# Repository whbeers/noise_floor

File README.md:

# Noise Floor interface board collection

This is set of interface boards to speed effect pedal development, continuing my efforts to learn PCB design with [KiCAD](https://www.kicad.org/).

### IO and Switch boards
The first board is an audio input and power board, featuring:
  - Switched DC barrel jack supporting either a 9VDC center negative supply or 9V battery
  - Mono audio jacks w/ switched input circuit (ring/ground shorted to sleeve on insertion)
  - Basic power input protection

The IO PCB is designed to fit in a standard 125B enclosure.

The second board simplifies effect bypass via a 3PDT switch adapter with an LED indicator.

#### Connectivity (cabled)
IO, Effect, and Switch boards are connected using four-circuit [Molex PicoBlade](https://www.molex.com/molex/products/family/picoblade?parentKey=wire_to_board_connectors) connectors.

Headers are labelled symmetrically from the perspective of the IO board:
 - **S**1 on IO Board <-> **S**1 on **S**witch Board
 - **S**2 on IO Board <-> **S**2 on **S**witch Board
 - **E**1 on IO Board <-> **E**1 on **E**ffect Board

### UX PCB (experimental)
The third and newest (experimental) board is a UX board providing a standard superset of potentiometers and switches. It is intended to connect to an effects board using two 25-position [Amphenol "Conan Lite"](https://www.amphenol-cs.com/product-series/conan-lite-1-00mm.html) board-to-board connectors.

The current iteration of the UX board supports six potentiometers and three SPDT switches, but alternative control layouts are an obvious extension. Each potentiometer on the current prototype can be adjusted using optional parallel resistors (SMD 1206) to tweak the taper and total resistance.

#### Connectivity (board-to-board)
The effect and UX boards are connected using [Amphenol "Conan Lite"](https://www.amphenol-cs.com/product-series/conan-lite-1-00mm.html) board-to-board connectors. Only a single UX board variety currently exists, supporting a superset of six potentiometers and three SPDT switches. As the UX board is in the experimental/proof-of-concept phase, the pin assignment should be considered preliminary and subject to change.

Current connector allocation:
 - 6x Potentiometers x 3 (CCW, Wiper, CW) = 18
 - 3x SPDT switches x 3 (NO, COM, NC) = 9
 - 4x Reserved for ground
 - Total used: 31
 - Remaining for expansion: 19
 
Ideas for future boards / changes:
 - Allocate connector positions for a single DPDT switch (+3, reusing 3 from an existing SPDT)
 - Incorporate linear potentiometers into an alternate IO board
 - Allocate at least 12 positions for "flexible use" (enough to support a 4PDT switch)
 - Allocate positions to drive (RGB?) LEDs with standardized current-limiting resistors

[Schematic PDF](schematics/noise_floor-latest.pdf)

## Credit

The original idea and specific bypass circuit is inspired by many manufacturers of utility PCBs and well-known circuits for 3PDT-based effect bypass, notably [PedalPCB's 3PDT breakout](https://www.pedalpcb.com/product/3pdt/), augmented to suit my needs.

Thanks as always to the folks on the [freestompboxes.org](https://www.freestompboxes.org/) forum for feedback and suggestions.

Potentiometer, 3PDT footswitch, and DC barrel jack 3D models courtesy [Vasily Kashirin](https://grabcad.com/vasily.kashirin-1).

SPDT toggle switch 3D model courtesy [Stephanie Schwecke](https://grabcad.com/stephanie.schwecke-1).

Conan Lite footprints adapted from the 51-position footprints available from SnapEDA: [Header](https://www.snapeda.com/parts/10162582-1134151LF/Amphenol%20ICC%20(FCI)/view-part/), [Receptacle](https://www.snapeda.com/parts/10162581-3134151LF/Amphenol%20ICC%20(FCI)/view-part/).([Additional license details](hardware/SnapEDA_Licensing.txt)). 3D models courtesy Amphenol.

*I am not affiliated with any of the brands, sites, or products named in this overview.*

## Future plans

 - Build an IO board that includes a TRS expression pedal input (started this way, but found it hard to fit in a 125B enclosure)
 - Support stereo operation via relays, optoisolators, or a "millenium" switch

## Versioning

My pcb designs utilize the following versioning scheme (I'll add to this as I produce more revisions):
 - v0.0XX: A candidate design that has not yet been produced and tested.
 - v0.XX: A design that has been produced, tested, and any initial errors addressed.

## Name
*The name Noise Floor is a reflection of the function of the board (a substrate for pedals and bypass circuit) and security nerdery.*

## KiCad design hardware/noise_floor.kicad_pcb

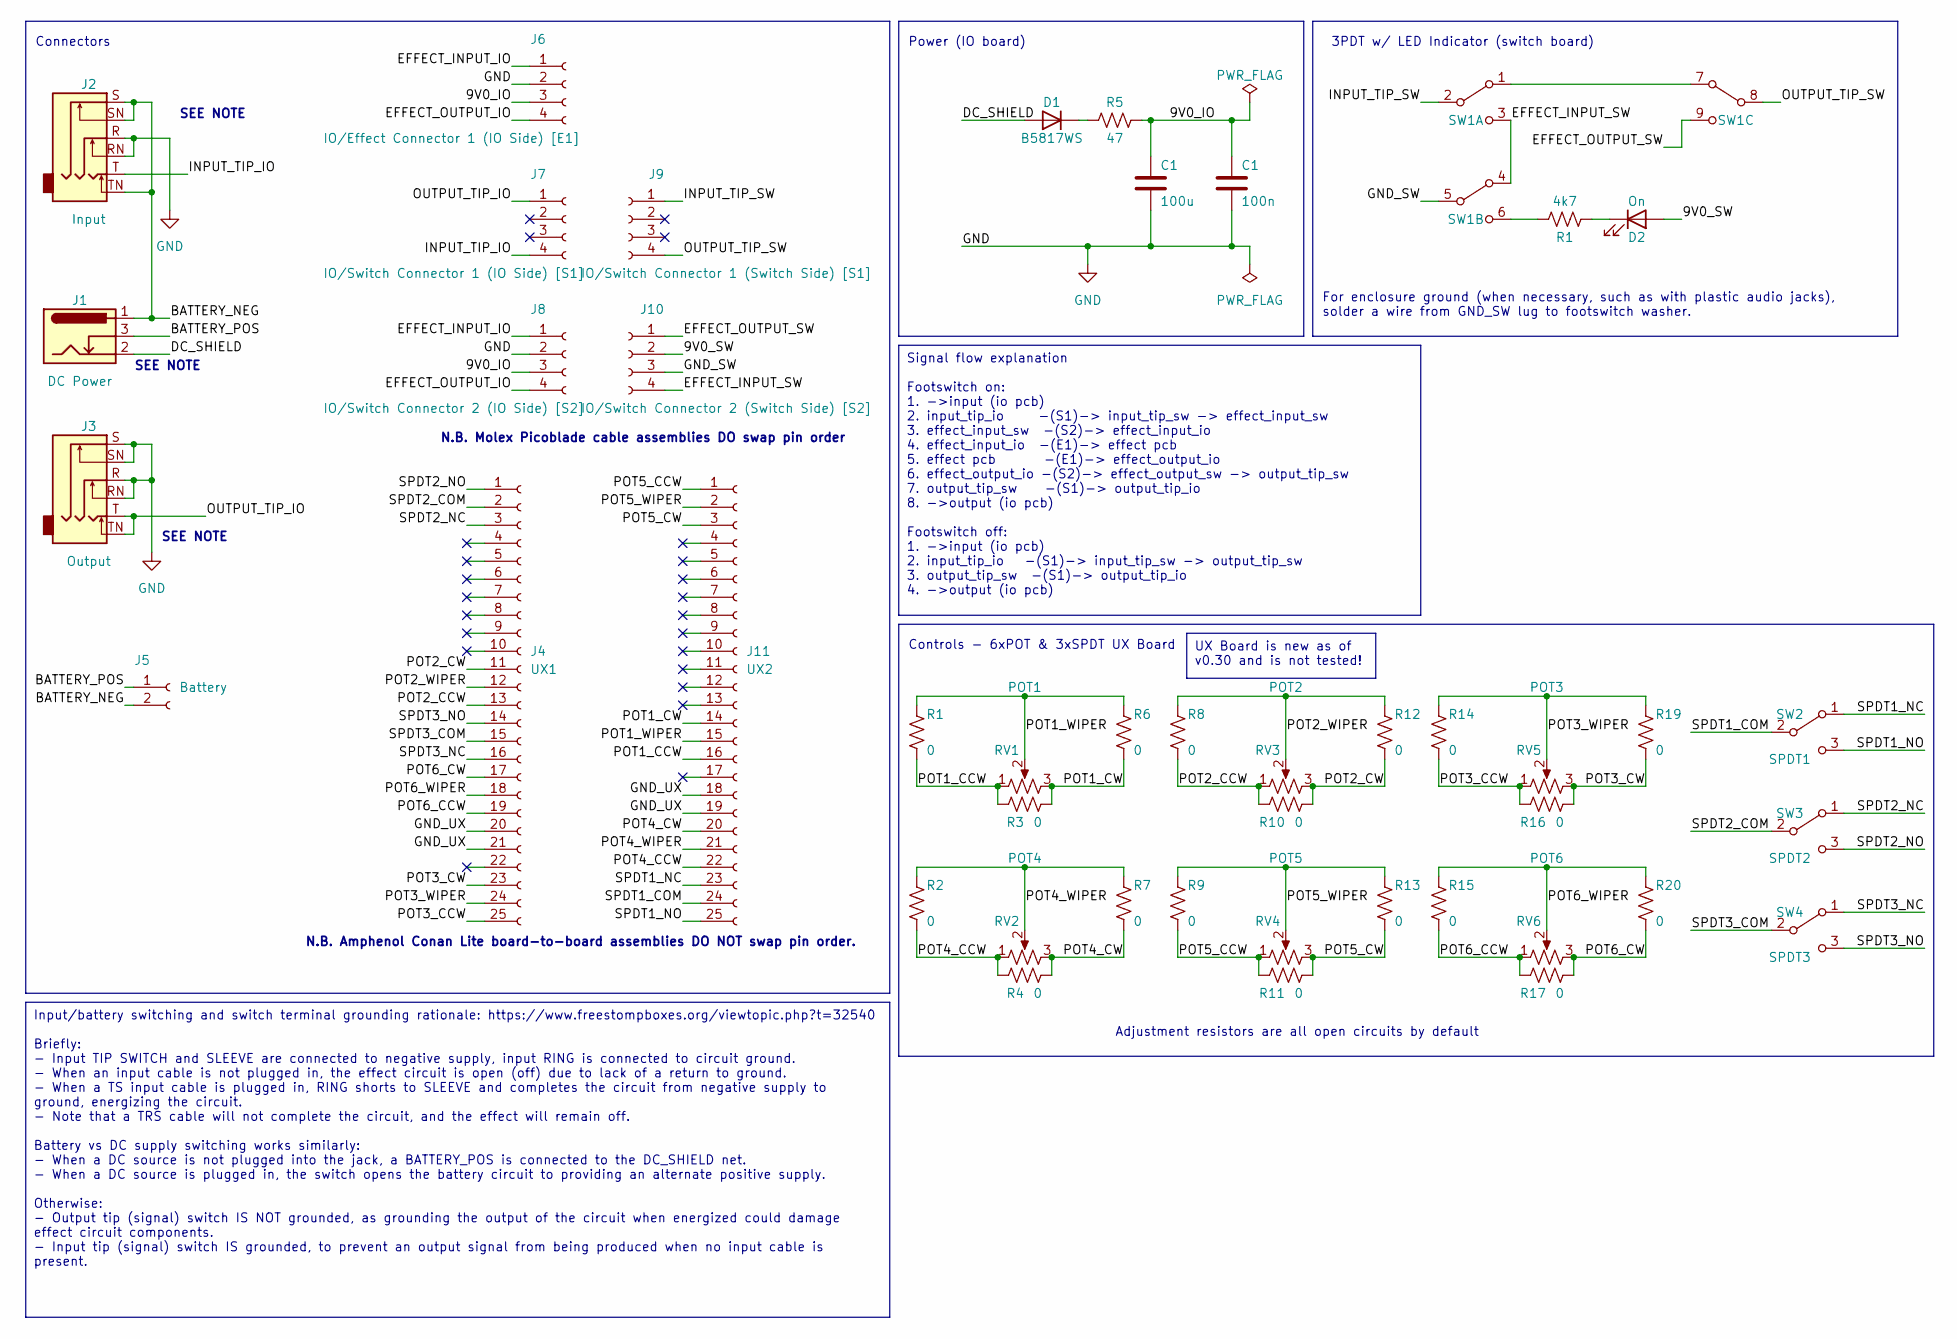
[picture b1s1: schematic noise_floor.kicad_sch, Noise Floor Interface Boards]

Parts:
C1: 100n; C_1206_3216Metric
D1: B5817WS; D_SOD-323_HandSoldering
D2: On; LED_D3.0mm
J1: DC Power; BarrelJack_GCT_DCJ200-10-A_Horizontal_with_3DModel_from_Vas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
J2: Input; ACJS-MHOM
J3: Output; ACJS-MHOM
J4: UX1; Amphenol_Receptacle_25pin_10162581-3134125LF
J5: Battery; JST_XH_B2B-XH-A_1x02_P2.50mm_Vertical
J6: IO/Effect Connector 1 (IO Side) [E1]; Molex_PicoBlade_53047-0410_1x04_P1.25mm_Vertical_with_3D_Mo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
J7: IO/Switch Connector 1 (IO Side) [S1]; Molex_PicoBlade_53047-0410_1x04_P1.25mm_Vertical_with_3D_Mo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
J8: IO/Switch Connector 2 (IO Side) [S2]; Molex_PicoBlade_53047-0410_1x04_P1.25mm_Vertical_with_3D_Mo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
J9: IO/Switch Connector 1 (Switch Side) [S1]; Molex_PicoBlade_53047-0410_1x04_P1.25mm_Vertical_with_3D_Mo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
J10: IO/Switch Connector 2 (Switch Side) [S2]; Molex_PicoBlade_53047-0410_1x04_P1.25mm_Vertical_with_3D_Mo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
J11: UX2; Amphenol_Receptacle_25pin_10162581-3134125LF
R1: 4k7; R_1206_3216Metric_Pad1.30x1.75mm_HandSolder
R2, R3, R4, R6, R7, R8, R9, R10, R11, R12, R13, R14, R15, R16, R17, R19, R20: 0; R_1206_3216Metric_Pad1.30x1.75mm_HandSolder
R5: 47; R_1206_3216Metric_Pad1.30x1.75mm_HandSolder
RV1: POT1; Potentiometer_Alpha_RD901F-40-00D_Single_Vertical_with_3DMo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
RV2: POT4; Potentiometer_Alpha_RD901F-40-00D_Single_Vertical_with_3DMo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
RV3: POT2; Potentiometer_Alpha_RD901F-40-00D_Single_Vertical_with_3DMo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
RV4: POT5; Potentiometer_Alpha_RD901F-40-00D_Single_Vertical_with_3DMo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
RV5: POT3; Potentiometer_Alpha_RD901F-40-00D_Single_Vertical_with_3DMo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
RV6: POT6; Potentiometer_Alpha_RD901F-40-00D_Single_Vertical_with_3DMo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
SW1: Footswitch; SW_3PDT_SOLDER_LUGS
SW2: SPDT1; SW_SPDT_SOLDER_LUGS
SW3: SPDT2; SW_SPDT_SOLDER_LUGS
SW4: SPDT3; SW_SPDT_SOLDER_LUGS

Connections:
/9V0_IO: C1.1, J6.3, J8.3, R5.1; also elsewhere on the board
/9V0_SW: D2.2 (A), J10.2
/BATTERY_NEG: J1.1, J2.S, J2.SN, J2.TN, J5.2
/BATTERY_POS: J1.3, J5.1
/DC_SHIELD: D1.2 (A), J1.2
/EFFECT_INPUT_IO: J6.1, J8.1
/EFFECT_INPUT_SW: J10.4, SW1.3 (A3), SW1.4 (B1)
/EFFECT_OUTPUT_IO: J6.4, J8.4
/EFFECT_OUTPUT_SW: J10.1, SW1.9 (C3)
/GND_SW: J10.3, SW1.5 (B2)
/GND_UX: J4.20, J4.21, J11.18, J11.19
/INPUT_TIP_IO: J2.T, J7.4
/INPUT_TIP_SW: J9.1, SW1.2 (A2)
/OUTPUT_TIP_IO: J3.T, J3.TN, J7.1
/OUTPUT_TIP_SW: J9.4, SW1.8 (C2)
/POT1_CW: J11.14, R3.1, R6.1, RV1.3
/POT2_CCW: J4.13, R8.1, R10.2, RV3.1
/POT2_CW: J4.11, R10.1, R12.1, RV3.3
/POT2_WIPER: J4.12, R8.2, R12.2, RV3.2
/POT3_CCW: J4.25, R14.1, R16.2, RV5.1
/POT3_CW: J4.23, R16.1, R19.1, RV5.3
/POT3_WIPER: J4.24, R14.2, R19.2, RV5.2
/POT4_CCW: J11.22, R2.1, R4.2, RV2.1
/POT4_CW: J11.20, R4.1, R7.1, RV2.3
/POT4_WIPER: J11.21, R2.2, R7.2, RV2.2
/POT5_CCW: J11.1, R9.1, R11.2, RV4.1
/POT5_CW: J11.3, R11.1, R13.1, RV4.3
/POT5_WIPER: J11.2, R9.2, R13.2, RV4.2
/POT6_CCW: J4.19, R15.1, R17.2, RV6.1
/POT6_CW: J4.17, R17.1, R20.1, RV6.3
/POT6_WIPER: J4.18, R15.2, R20.2, RV6.2
/SPDT1_COM: J11.24, SW2.2 (B)
/SPDT1_NC: J11.23, SW2.1 (A)
/SPDT1_NO: J11.25, SW2.3 (C)
/SPDT2_COM: J4.2, SW3.2 (B)
/SPDT2_NC: J4.3, SW3.1 (A)
/SPDT2_NO: J4.1, SW3.3 (C)
/SPDT3_COM: J4.15, SW4.2 (B)
/SPDT3_NC: J4.16, SW4.1 (A)
/SPDT3_NO: J4.14, SW4.3 (C)
GND: C1.2, J2.R, J2.RN, J3.R, J3.RN, J3.S, J3.SN, J6.2, J8.2; also elsewhere on the board
unnamed: D1.1 (K), R5.2
unnamed: SW1.1 (A1), SW1.7 (C1)

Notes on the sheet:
Input/battery switching and switch terminal grounding rationale: https://www.freestompboxes.org/viewtopic.php?t=32540 Briefly: - Input TIP SWITCH and SLEEVE are connected to negative supply, input RING is connected to circuit ground. - When an input cable is not plugged in, the effect circuit is op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
Signal flow explanation Footswitch on: 1. ->input (io pcb) 2. input_tip_io -(S1)-> input_tip_sw -> effect_input_sw 3. effect_input_sw -(S2)-> effect_input_io 4. effect_input_io -(E1)-> effect pcb 5. effect pcb -(E1)-> effect_output_io 6. effect_output_io -(S2)-> effect_output_sw -> output_tip_sw 7.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
UX Board is new as of v0.30 and is not tested!
Connectors
For enclosure ground (when necessary, such as with plastic audio jacks), solder a wire from GND_SW lug to footswitch washer.
3PDT w/ LED Indicator (switch board)
SEE NOTE
Power (IO board)
Controls - 6xPOT & 3xSPDT UX Board
N.B. Amphenol Conan Lite board-to-board assemblies DO NOT swap pin order.
Adjustment resistors are all open circuits by default
N.B. Molex Picoblade cable assemblies DO swap pin order

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
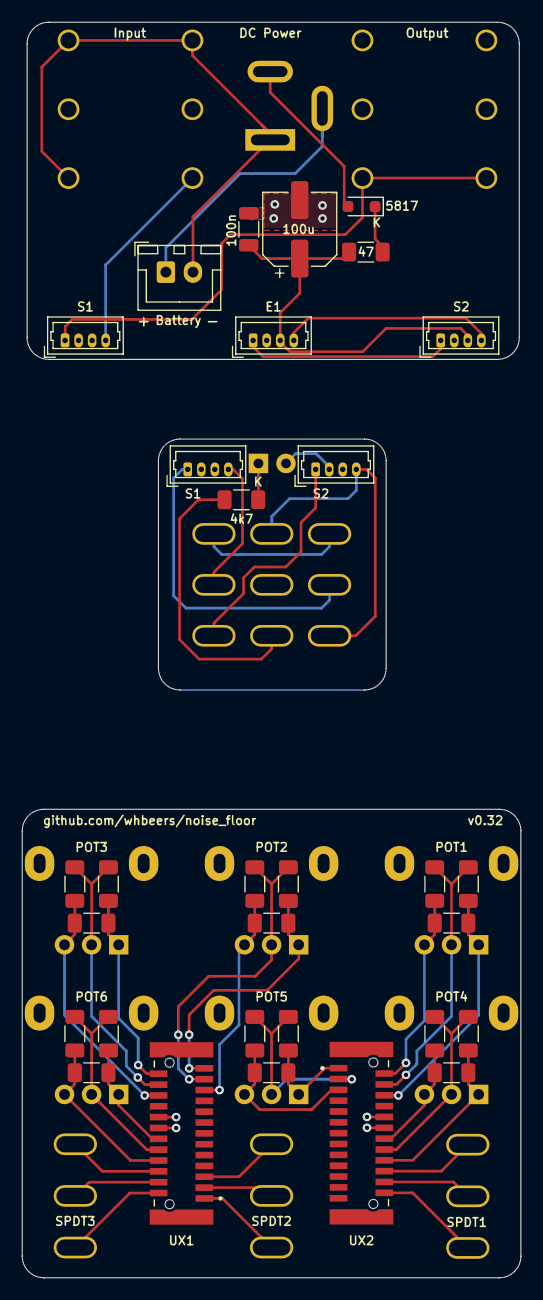
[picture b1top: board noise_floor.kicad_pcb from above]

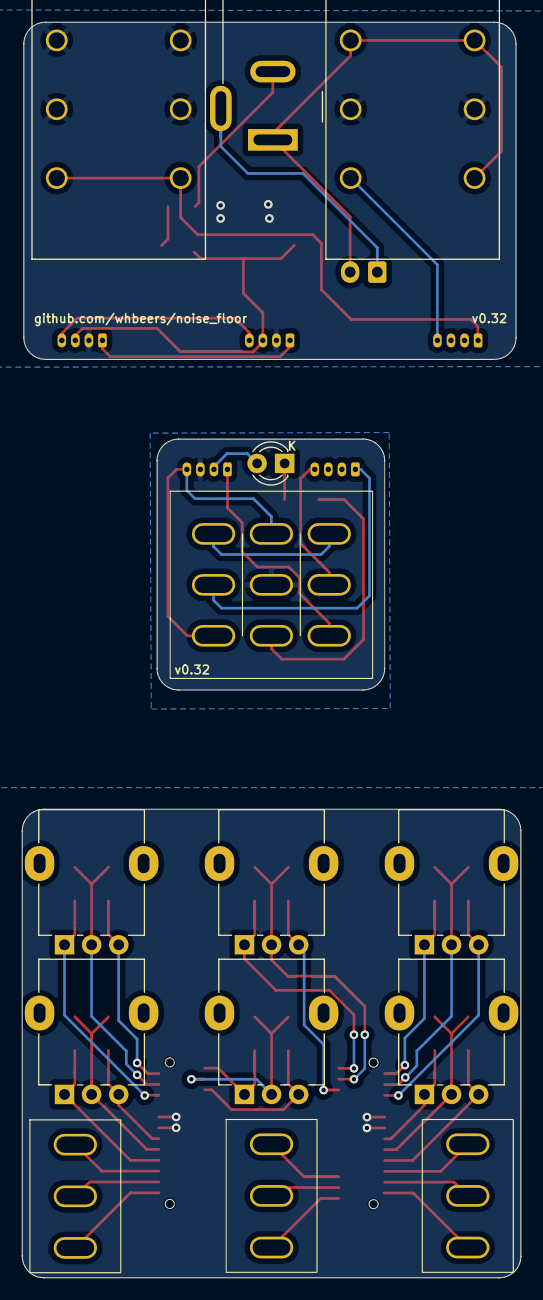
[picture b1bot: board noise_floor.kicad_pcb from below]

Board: 2 copper layers, 46.0 x 115.8 mm, 45 parts (14 on the bottom side), 47 nets.

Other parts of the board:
C2: 100n; C_1206_3216Metric
R18: 4k7; R_1206_3216Metric_Pad1.30x1.75mm_HandSolder

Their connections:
/9V0_IO: C2.1; also elsewhere on the board
GND: C2.2; also elsewhere on the board

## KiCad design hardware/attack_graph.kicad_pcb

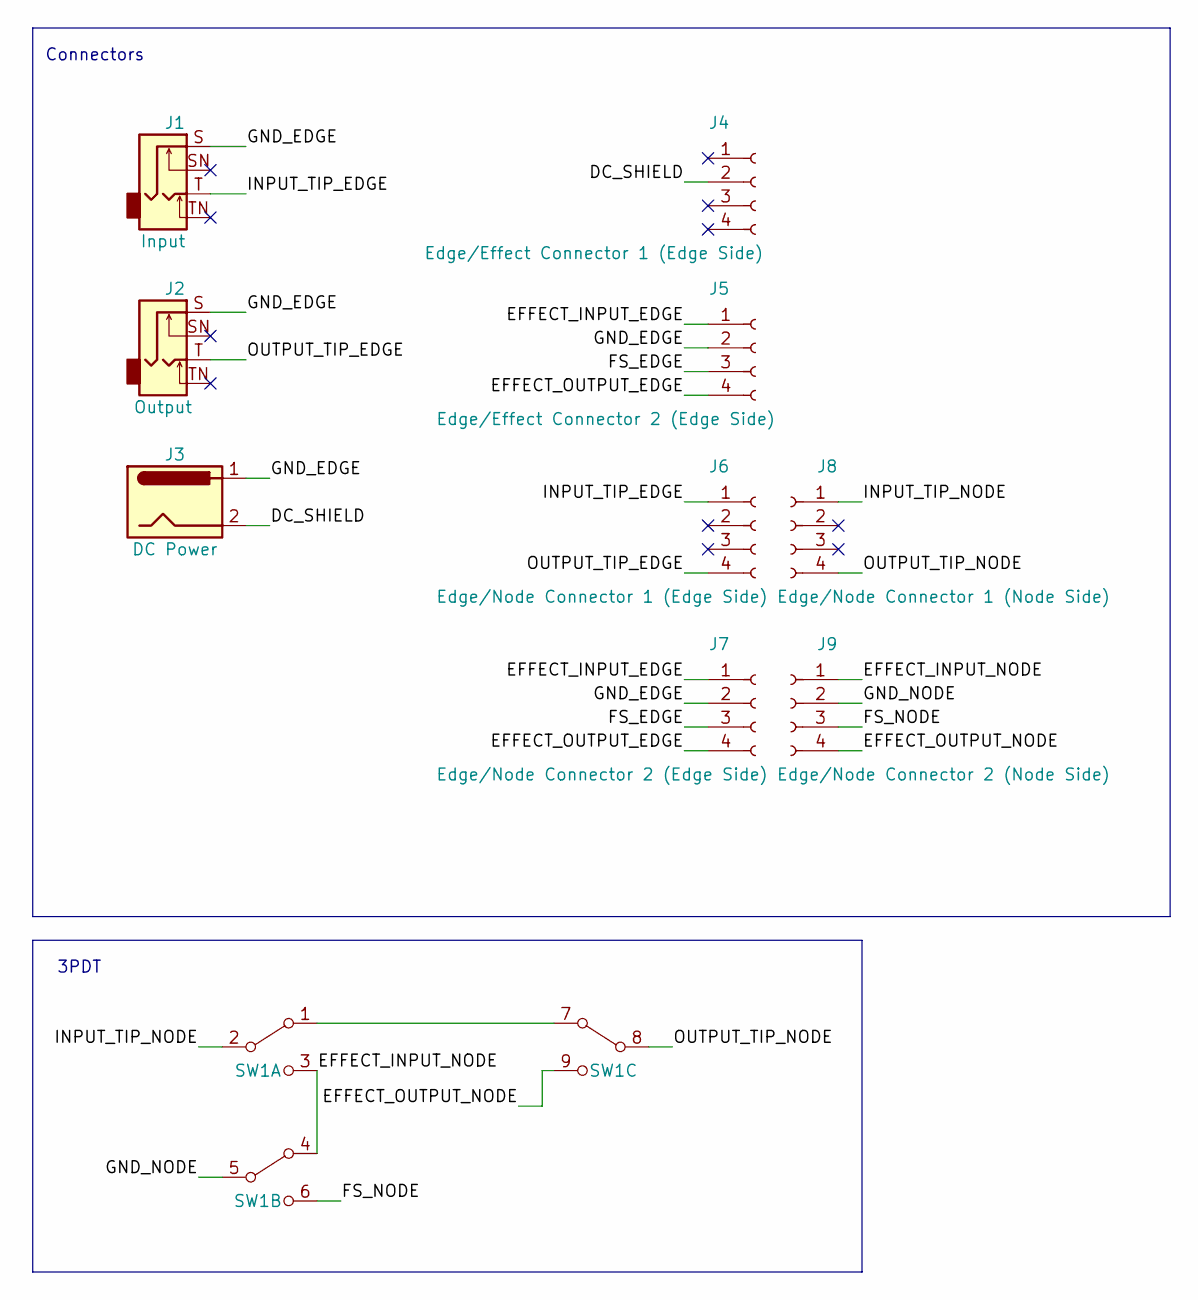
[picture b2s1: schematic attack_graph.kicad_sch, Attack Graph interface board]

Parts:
J1: Input; Jack_6.35mm_Neutrik_NMJ4HCD2_Horizontal
J2: Output; Jack_6.35mm_Neutrik_NMJ4HCD2_Horizontal
J3: DC Power; BarrelJack_GCT_DCJ200-10-A_Horizontal
J4: Edge/Effect Connector 1 (Edge Side); Molex_PicoBlade_53047-0410_1x04_P1.25mm_Vertical
J5: Edge/Effect Connector 2 (Edge Side); Molex_PicoBlade_53047-0410_1x04_P1.25mm_Vertical
J6: Edge/Node Connector 1 (Edge Side); Molex_PicoBlade_53047-0410_1x04_P1.25mm_Vertical
J7: Edge/Node Connector 2 (Edge Side); Molex_PicoBlade_53047-0410_1x04_P1.25mm_Vertical
J8: Edge/Node Connector 1 (Node Side); Molex_PicoBlade_53047-0410_1x04_P1.25mm_Vertical
J9: Edge/Node Connector 2 (Node Side); Molex_PicoBlade_53047-0410_1x04_P1.25mm_Vertical
SW1: Footswitch; SW_3PDT_SOLDER_LUGS

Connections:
/DC_SHIELD: J3.2, J4.2
/EFFECT_INPUT_EDGE: J5.1, J7.1
/EFFECT_INPUT_NODE: J9.1, SW1.3 (A3), SW1.4 (B1)
/EFFECT_OUTPUT_EDGE: J5.4, J7.4
/EFFECT_OUTPUT_NODE: J9.4, SW1.9 (C3)
/FS_EDGE: J5.3, J7.3
/FS_NODE: J9.3, SW1.6 (B3)
/GND_EDGE: J1.S, J2.S, J3.1, J5.2, J7.2
/GND_NODE: J9.2, SW1.5 (B2)
/INPUT_TIP_EDGE: J1.T, J6.1
/INPUT_TIP_NODE: J8.1, SW1.2 (A2)
/OUTPUT_TIP_EDGE: J2.T, J6.4
/OUTPUT_TIP_NODE: J8.4, SW1.8 (C2)
unnamed: SW1.1 (A1), SW1.7 (C1)

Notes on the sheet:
Connectors
3PDT

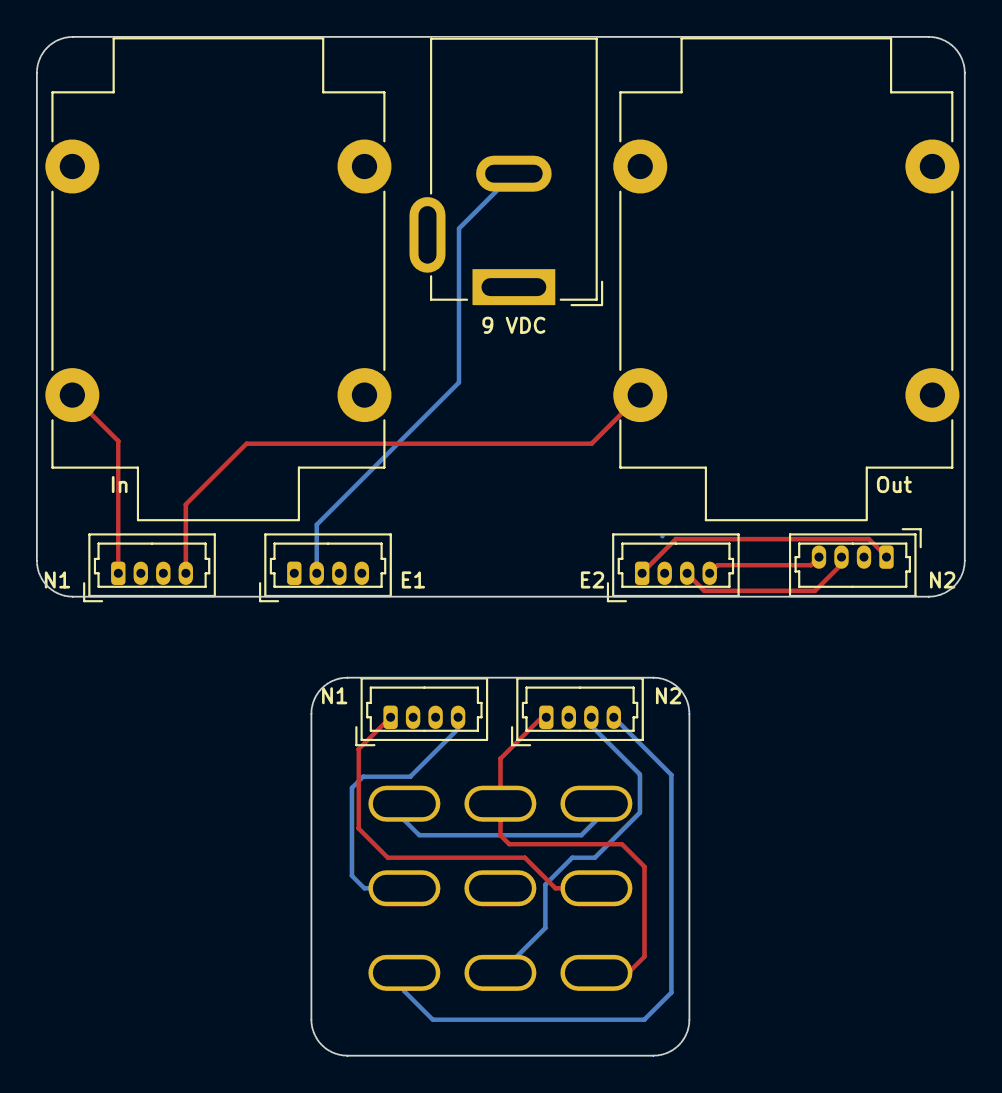
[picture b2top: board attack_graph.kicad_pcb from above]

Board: 2 copper layers, 51.5 x 56.6 mm, 10 parts (1 on the bottom side), 14 nets.

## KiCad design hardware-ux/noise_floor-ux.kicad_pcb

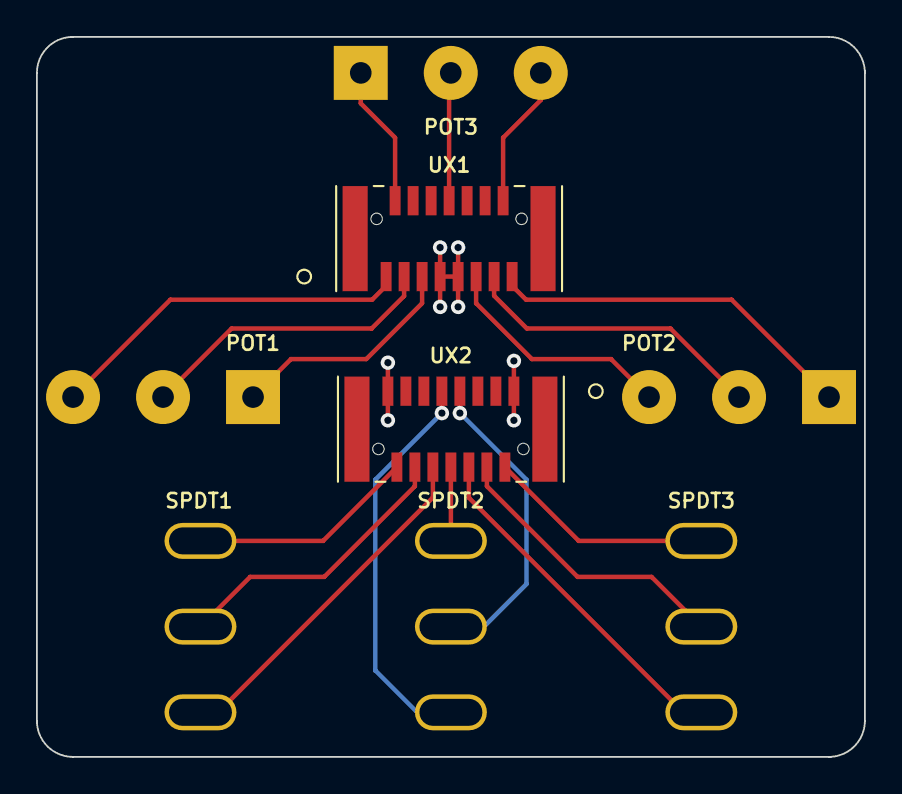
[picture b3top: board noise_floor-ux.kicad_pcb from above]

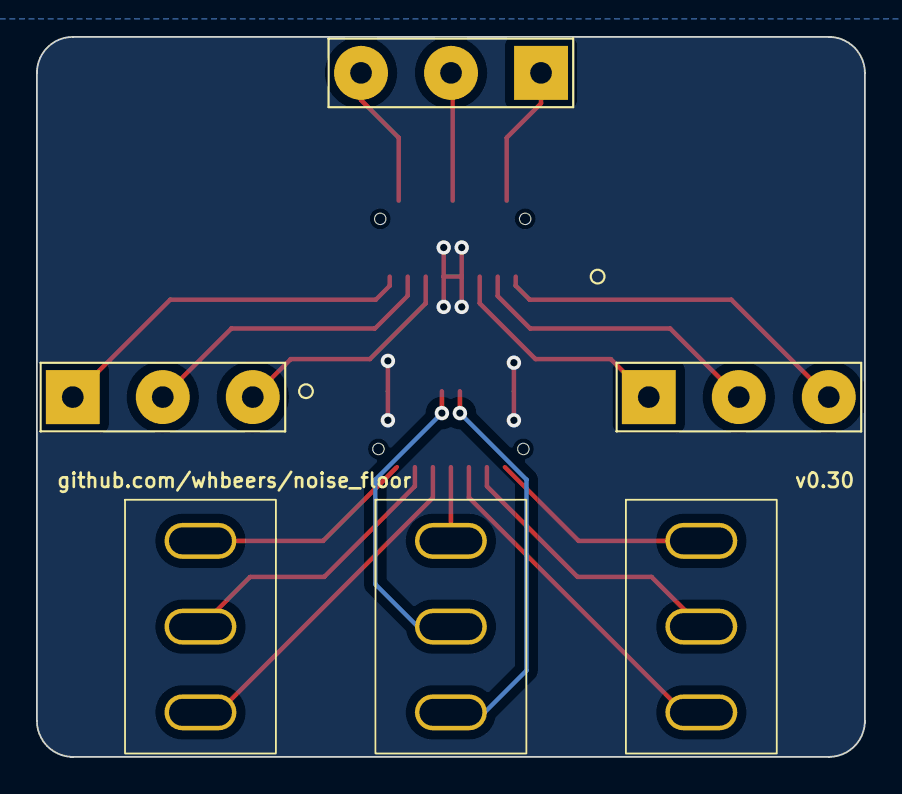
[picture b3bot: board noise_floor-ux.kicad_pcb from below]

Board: 2 copper layers, 46.0 x 40.0 mm, 8 parts (6 on the bottom side), 19 nets.

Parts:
J4: UX1; Amphenol_Receptacle_15pin_10162581-3134115LF
J5: UX2; Amphenol_Receptacle_15pin_10162581-3134115LF
RV1: POT1; Potentiometer_Single_3_Horizontal
RV2: POT2; Potentiometer_Single_3_Horizontal
RV3: POT3; Potentiometer_Single_3_Horizontal
SW1: SPDT1; SW_SPDT_SOLDER_LUGS
SW2: SPDT2; SW_SPDT_SOLDER_LUGS
SW3: SPDT3; SW_SPDT_SOLDER_LUGS

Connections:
Board_0-/GND_UX: J4.7, J4.9, J5.1, J5.15
Board_0-/POT1_CCW: J4.5, RV1.1
Board_0-/POT1_CW: J4.1, RV1.3
Board_0-/POT1_WIPER: J4.3, RV1.2
Board_0-/POT2_CCW: J4.15, RV2.1
Board_0-/POT2_CW: J4.11, RV2.3
Board_0-/POT2_WIPER: J4.13, RV2.2
Board_0-/POT3_CCW: J4.2, RV3.1
Board_0-/POT3_CW: J4.14, RV3.3
Board_0-/POT3_WIPER: J4.8, RV3.2
Board_0-/SPDT1_COM: J5.12, SW1.2 (B)
Board_0-/SPDT1_NC: J5.14, SW1.1 (A)
Board_0-/SPDT1_NO: J5.10, SW1.3 (C)
Board_0-/SPDT2_COM: J5.7, SW2.2 (B)
Board_0-/SPDT2_NC: J5.8, SW2.1 (A)
Board_0-/SPDT2_NO: J5.9, SW2.3 (C)
Board_0-/SPDT3_COM: J5.4, SW3.2 (B)
Board_0-/SPDT3_NC: J5.2, SW3.1 (A)
Board_0-/SPDT3_NO: J5.6, SW3.3 (C)

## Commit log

2023-03-02 initial checkin for attack graph utility pcb design v0.01
2023-03-02 change name to Noise Floor
2023-03-03 fix ordering of IO/Switch board connectors
2023-03-03 Offload DC protection and LED indicator to "noise floor" utility boards
    - much rerouting and layout work, but functionally the same
2023-03-03 fix minor layout issue
2023-03-03 rename schematic file with version number
2023-03-03 bump version number on schematic, oops
2023-03-03 v0.03 updates:
    - switch to SMD resistor and diode to save space (particularly on footswitch board)
    - move IO and DC jacks to bottom of board and ensure they're on the correct side
    - consolidate to a single effect board connector.
2023-03-04 update gitignore, random inconsequential changes to accomodate splitting boards
2023-03-04 Some updates based on feedback from freestompboxes.org folks:
    - Add back thermal reliefs on ground pads
    - Switch to stereo jacks for improved mechanical support
    - Use switched symbol/footprint for DC Barrel jack, correct circuit to suit (still need to add switching on input jack)
    - Add 3D models for various parts (courtesy of Vasily Kashirin - https://grabcad.com/vasily.kashirin-1/models?page=1)
2023-03-04 fix a couple DRCs and bump rev
2023-03-05 v0.05, added switched power input and optional battery connection
2023-03-05 Remove ground from output switch line, fix ground split ground plane
2023-03-05 slight adjustment to input switch behavior, add note about chassis ground
2023-03-05 add script to generate schematic, saving time at release. also embed an SVG schematic in README.
2023-03-05 update script to extract revision
2023-03-05 remove version note from README
2023-03-05 add script to split into io and switch board, then export gerbers
2023-03-08 add amphenol phone jack footprint
2023-03-10 update schematic plotting script to create the directory if it doesn't exist
2023-03-10 Fix errata from v0.03 prototype inspection:
    - Switch to narrower amphenol phone jacks to better fit within 125B enclosure
    - Swap pin ordering for picoblade connections on IO board, as retail cable assemblies swap pin order
    -
    Also:
    - Add JST XH header for battery connection
    Another commit will complete the reroute shortly.
2023-03-10 finish routing for v0.1 revision
2023-03-11 rearrange layout of schematic
2023-03-11 and plot updated schematic
2023-03-13 Update to latest stable kicad version:
    - fixed issue rendering certain 3d models in color
    - had to fix some text rendering changes
2023-03-16 Address issues identified in hardware rev v0.1
    - ACJS-MHOM footprint was pinned backwards. Confirmed operation when flipped to other side of board + rotated backwards.
    - Fix silkscreen: Move DC jack label within board bounds, add battery +/- indicators
    - Slightly shift DC power jack to better align to enclosure bounds.
2023-03-17 add disclaimer
2023-03-24 Fix one issue discovered in testing of v0.2 hardware
    - swap nets on battery JST connector
2023-03-26 improve power filtering and move to more SMD components
2023-03-27 v0.30 includes a new "ux" board, with the initial feature set:
    - board-to-board connector interface for expandability
    - three potentiometers and three SPDT switches
2023-03-27 renders for v0.30
2023-03-27 Add pot adjustment resistors, adapt to different layout and reroute, bump to v0.31
2023-03-27 Further iteration on UX board:
    - Change to square body pots and bump count to six
    - Change to 25-pin board-to-board connectors (and improve footprint)
    - Change optional pot adjustment to 1206 smt resistors
    - Update layout/routing to suit
2023-03-27 remove unused pot model, add snapeda licensing info
2023-03-27 minor tweaks to schematic layout
2023-03-31 Update README.md
    typo
